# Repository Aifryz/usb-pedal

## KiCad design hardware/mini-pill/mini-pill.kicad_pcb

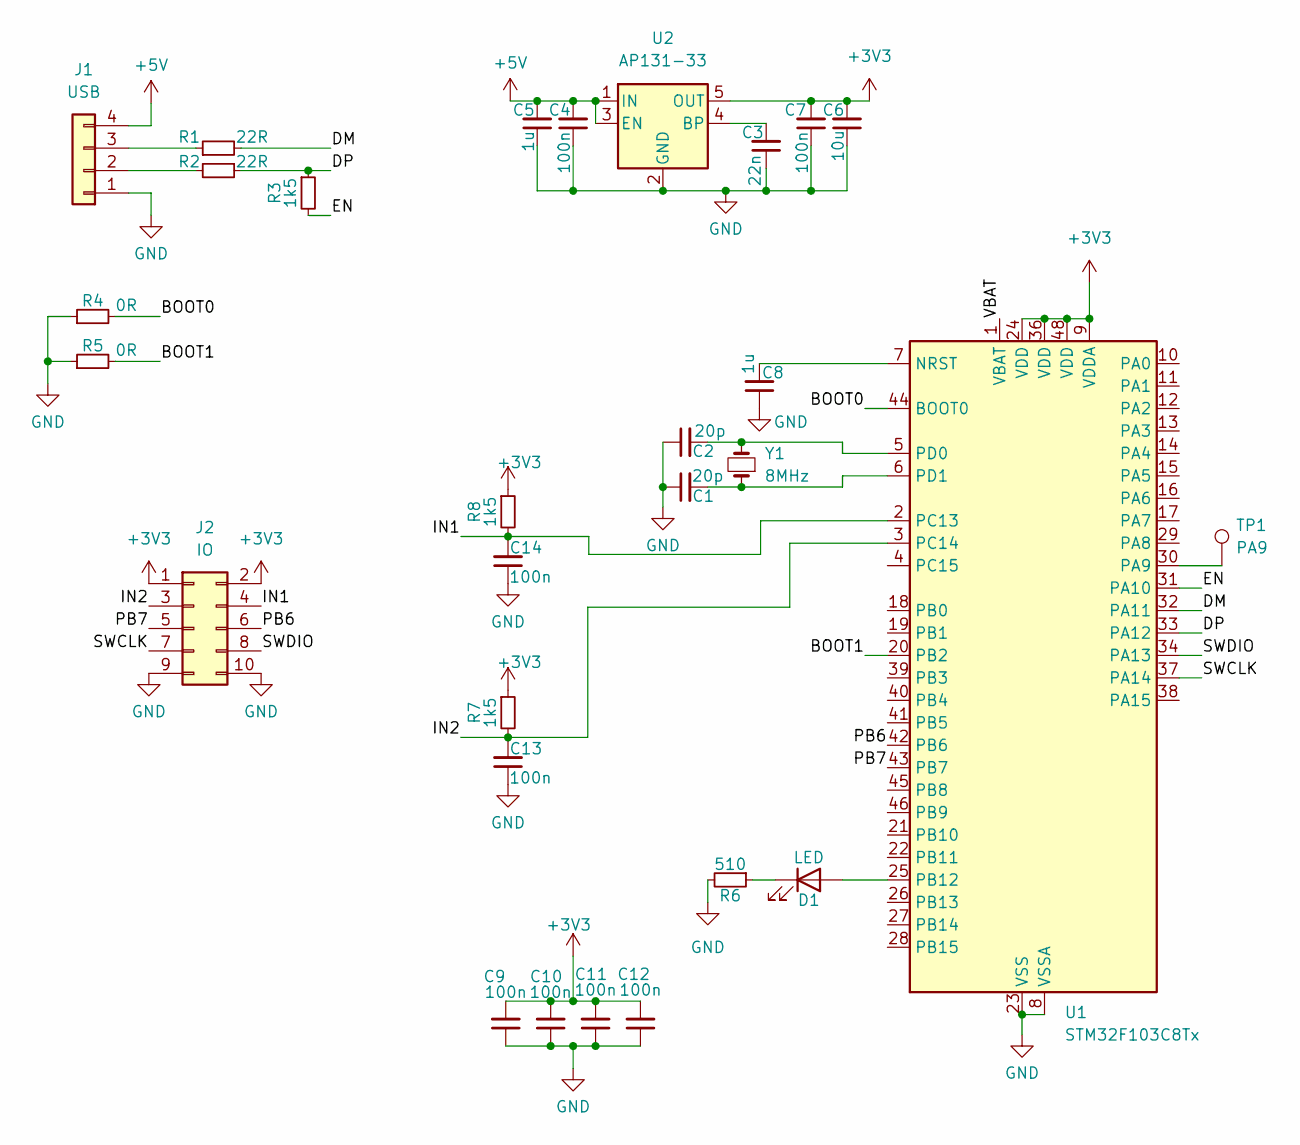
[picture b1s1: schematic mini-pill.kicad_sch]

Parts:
C1, C2: 20p; C_0603_1608Metric
C3: 22n; C_0603_1608Metric
C4, C7, C9, C10, C11, C12, C13, C14: 100n; C_0603_1608Metric
C5, C8: 1u; C_0603_1608Metric
C6: 10u; C_0805_2012Metric
D1: LED; LED_0805_2012Metric
J1: USB; PinSocket_1x04_P2.00mm_Vertical
J2: IO; PinHeader_2x05_P2.54mm_Vertical
R1, R2: 22R; R_0603_1608Metric
R3, R7, R8: 1k5; R_0603_1608Metric
R4, R5: 0R; R_0603_1608Metric
R6: 510; R_0603_1608Metric
TP1: PA9; TestPoint_Pad_D1.0mm
U1: STM32F103C8Tx; LQFP-48_7x7mm_P0.5mm
U2: AP131-33; SOT-23-5
Y1: 8MHz; Crystal_HC18-U_Vertical

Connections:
+3V3: C6.2, C7.2, C9.2, C10.2, C11.2, C12.2, J2.1, J2.2, R7.1, R8.1, U1.9 (VDDA), U1.24 (VDD), U1.36 (VDD), U1.48 (VDD), U2.5 (OUT)
+5V: C4.2, C5.2, J1.4, U2.1 (IN), U2.3 (EN)
/BOOT0: R4.2, U1.44 (BOOT0)
/BOOT1: R5.2, U1.20 (PB2)
/DM: R1.2, U1.32 (PA11)
/DP: R2.1, R3.1, U1.33 (PA12)
/EN: R3.2, U1.31 (PA10)
/IN1: C14.2, J2.4, R8.2, U1.2 (PC13)
/IN2: C13.2, J2.3, R7.2, U1.3 (PC14)
/PB6: J2.6, U1.42 (PB6)
/PB7: J2.5, U1.43 (PB7)
/SWCLK: J2.7, U1.37 (PA14)
/SWDIO: J2.8, U1.34 (PA13)
/VBAT: U1.1 (VBAT)
GND: C1.1, C2.1, C3.1, C4.1, C5.1, C6.1, C7.1, C8.1, C9.1, C10.1, C11.1, C12.1, C13.1, C14.1, J1.1, J2.9, J2.10, R4.1, R5.1, R6.2, U1.8 (VSSA), U1.23 (VSS), U1.35 (VSS), U1.47 (VSS), U2.2 (GND)
unnamed: D1.2 (A), U1.25 (PB12)
unnamed: D1.1 (K), R6.1
unnamed: J1.2, R2.2
unnamed: J1.3, R1.1
unnamed: C8.2, U1.7 (NRST)
unnamed: TP1.1, U1.30 (PA9)
unnamed: C2.2, U1.5 (PD0), Y1.2
unnamed: C1.2, U1.6 (PD1), Y1.1
unnamed: C3.2, U2.4 (BP)

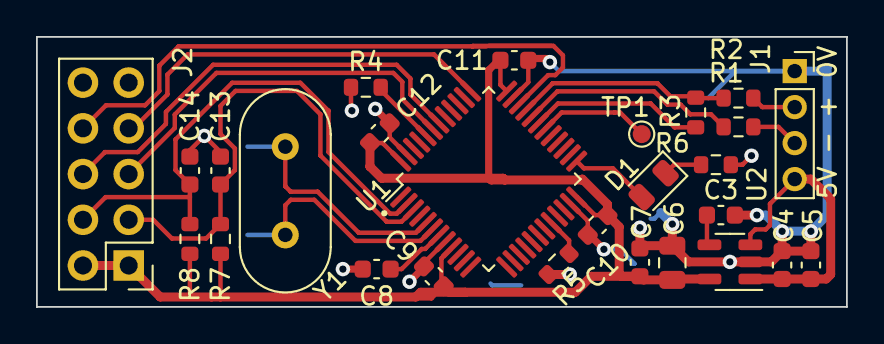
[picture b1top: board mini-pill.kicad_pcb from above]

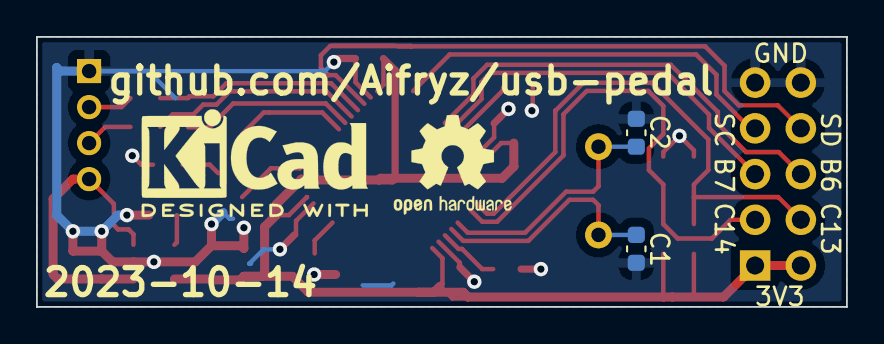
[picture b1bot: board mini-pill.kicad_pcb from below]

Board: 2 copper layers, 45.0 x 15.0 mm, 29 parts (2 on the bottom side), 23 nets.

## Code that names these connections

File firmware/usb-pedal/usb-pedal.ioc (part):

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Mcu.Name=STM32F103C(8-B)Tx
Mcu.Package=LQFP48
Mcu.UserName=STM32F103C8Tx
PA10.GPIOParameters=GPIO_Label
PA10.GPIO_Label=USB_EN
PA10.Signal=GPIO_Output
PA11.Mode=Device
PA11.Signal=USB_DM
PA12.Mode=Device
PA12.Signal=USB_DP
PA13.Mode=Serial_Wire
PA13.Signal=SYS_JTMS-SWDIO
PA14.Mode=Serial_Wire
PA14.Signal=SYS_JTCK-SWCLK
PB12.GPIOParameters=GPIO_Label
PB12.GPIO_Label=LED
PB12.Signal=GPIO_Output
PB6.Signal=GPIO_Input
PB7.Signal=GPIO_Input
PC13-TAMPER-RTC.GPIOParameters=GPIO_Label
PC13-TAMPER-RTC.GPIO_Label=IN1
PC13-TAMPER-RTC.Signal=GPIO_Input
PC14-OSC32_IN.GPIOParameters=GPIO_Label
PC14-OSC32_IN.GPIO_Label=IN2
PC14-OSC32_IN.Signal=GPIO_Input
PD0-OSC_IN.Mode=HSE-External-Oscillator
PD0-OSC_IN.Signal=RCC_OSC_IN
PD1-OSC_OUT.Mode=HSE-External-Oscillator
PD1-OSC_OUT.Signal=RCC_OSC_OUT
RCC.SYSCLKFreq_VALUE=72000000
RCC.SYSCLKSource=RCC_SYSCLKSOURCE_PLLCLK
board=custom

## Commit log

2023-10-12 Add pcb
2023-10-14 Add schematic
2023-11-04 Add base project
2023-11-12 Add basic key input
